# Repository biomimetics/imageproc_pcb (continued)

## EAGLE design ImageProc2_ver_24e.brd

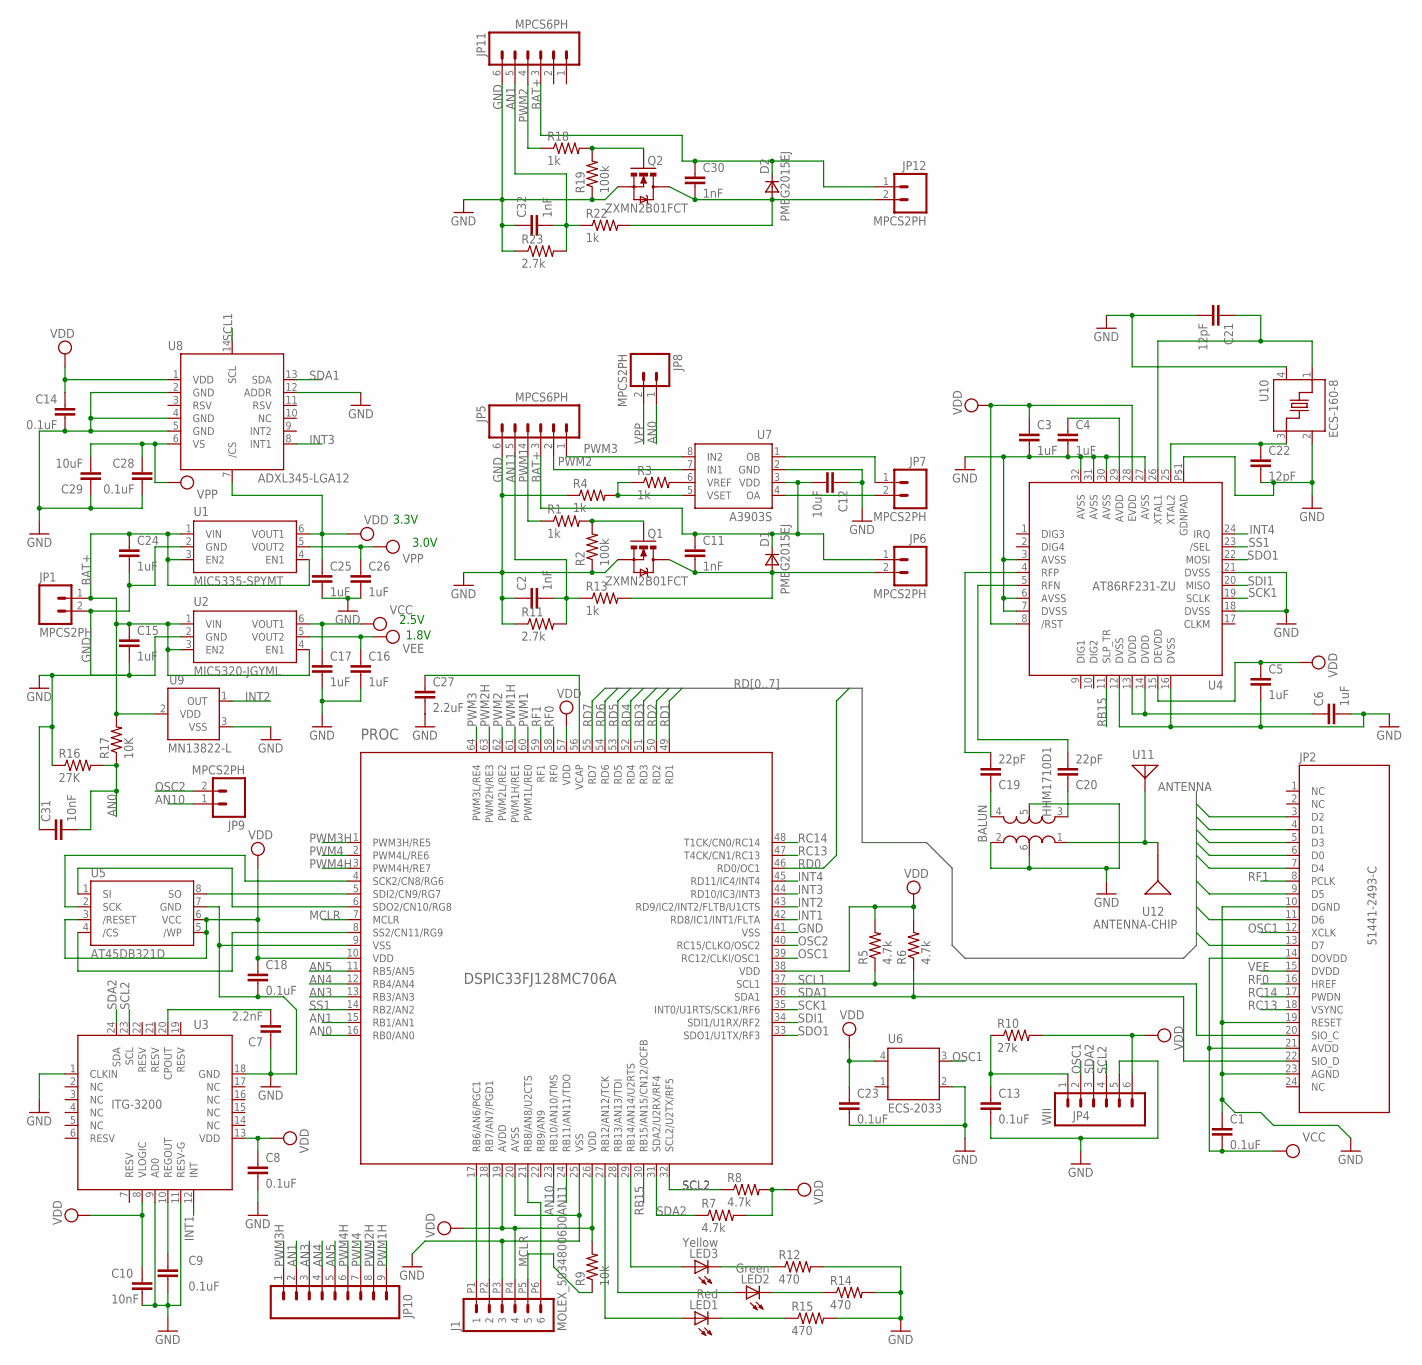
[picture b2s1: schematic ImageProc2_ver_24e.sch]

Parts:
BALUN: HHM1710D1; BALUN; DIGIKEY 445-3246-1-ND
C1, C8, C9, C13, C14, C18, C23, C28: 0.1uF; 0402-CAP; DIGIKEY 490-1318-1-ND
C2, C11, C30, C32: 1nF; 0402-CAP; DIGIKEY 490-1303-1-ND
C3, C4, C5, C6, C15, C16, C17, C24, C25, C26: 1uF; 0402-CAP; DIGIKEY 445-4998-1-ND
C7: 2.2nF; 0402-CAP; DIGIKEY 399-1033-1-ND
C10, C31: 10nF; 0402-CAP; DIGIKEY 399-1279-1-ND
C12, C29: 10uF; 0603-CAP; DIGIKEY 399-5504-1-ND
C19, C20: 22pF; 0402-CAP; DIGIKEY 490-1283-1-ND
C21, C22: 12pF; 0402-CAP; DIGIKEY 490-3115-1-ND
C27: 2.2uF; 0402-CAP; DIGIKEY C1005X5R0G225M
D1, D2: PMEG2015EJ; SOD323; DIGIKEY 568-4117-1-ND
J1: MOLEX_5034800600; DIGIKEY WM1387CT-ND
JP1, JP6, JP7, JP8, JP9, JP12: MPCS2PH; MOLEX-PICO_CLASP_S2P
JP2: 51441-2493-C; MOLEX-52740-2490; DIGIKEY WM1561-ND
JP4: WII; MOLEX-PICO_CLASP_S6P
JP5, JP11: MPCS6PH; MOLEX-PICO_CLASP_S6P
JP10: SOLDER_PADS_9P
LED1: Red; CHIP-LED0603; DIGIKEY 67-1690-1-ND
LED2: Green; CHIP-LED0603; DIGIKEY 67-1693-1-ND
LED3: Yellow; CHIP-LED0603; DIGIKEY 67-1694-1-ND
PROC: DSPIC33FJ128MC706A; TQFP64; DIGIKEY DSPIC33FJ128MC706A-I/PT-ND
Q1, Q2: ZXMN2B01FCT; SOT23-3; DIGIKEY ZXMN2B01FCT-ND
R1, R3, R4, R13, R18, R22: 1k; R0402; DIGIKEY P1.0KJCT-ND
R2, R19: 100k; R0402; DIGIKEY P100KJCT-ND
R5, R6, R7, R8: 4.7k; R0402; DIGIKEY P4.7KJCT-ND
R9: 10k; R0402; DIGIKEY P10KJCT-ND
R10: 27k; R0402; DIGIKEY P27KJCT-ND
R11, R23: 2.7k; R0402; DIGIKEY P2.7KJCT-ND
R12, R14, R15: 470; R0402; DIGIKEY 541-470JCT-ND
R16: 27K; R0402; DIGIKEY P27KJCT-ND
R17: 10K; R0402; DIGIKEY P10KJCT-ND
U1: MIC5335-SPYMT; MLF-6; DIGIKEY 576-1949-1-ND
U2: MIC5320-JGYML; MLF-6; DIGIKEY 576-3589-6-ND
U3: ITG-3200; QFN-24
U4: AT86RF231-ZU; QFN-32; DIGIKEY AT86RF231-ZU-ND
U5: AT45DB321D; MLF(VDFN)-8; DIGIKEY AT45DB321D-SU-ND
U6: ECS-2033; OSCILLATOR-SMD; DIGIKEY XC1437CT-ND
U7: A3903S; DFN-8; DIGIKEY 620-1205-1-ND
U8: ADXL345-LGA12; LGA14; DIGIKEY ADXL345BCCZ-RLCT-ND
U9: MN13822-L; SOT-23-3; DIGIKEY 497-6182-1-ND
U10: ECS-160-8; CRYSTAL-SMD; DIGIKEY ECS-160-20-33-CKM-TR
U11: ANTENNA; ANTENNA_PAD
U12: ANTENNA-CHIP; DIGIKEY 445-3719-1-ND

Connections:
AN0: C31.2, JP8.1, PROC.16 (RB0/AN0), R16.2, R17.1
AN1: C32.2, JP10.2, JP11.5, PROC.15 (RB1/AN1), R22.1, R23.2
AN3: JP10.3, PROC.13 (RB3/AN3)
AN4: JP10.4, PROC.12 (RB4/AN4)
AN5: JP10.5, PROC.11 (RB5/AN5)
AN10: JP9.1, PROC.23 (RB10/AN10/TMS)
AN11: C2.2, JP5.5, PROC.24 (RB11/AN11/TDO), R11.2, R13.1
BAT+: C11.1, C12.2, C15.1, C24.1, C30.1, D1.1 (C), D2.1 (C), JP1.1, JP5.3, JP6.1, JP11.3, JP12.1, R17.2, U1.1 (VIN), U1.3 (EN2), U1.4 (EN1), U2.1 (VIN), U2.3 (EN2), U2.4 (EN1), U7.3 (VDD), U9.2 (VDD)
GND: BALUN.2 (RFGND), BALUN.5 (GND), BALUN.6 (NC), C1.1, C2.1, C3.2, C4.2, C5.2, C6.2, C7.1, C8.2, C9.2, C10.2, C12.1, C13.2, C14.2, C15.2, C16.2, C17.2, C18.2, C21.2, C22.2, C23.2, C24.2, C25.2, C26.2, C27.2, C28.2, C29.1, C31.1, C32.1, J1.P3 (3), JP1.2, JP2.10 (DGND), JP2.19 (RESET), JP2.23 (AGND), JP4.5, JP5.6, JP11.6, PROC.9 (VSS), PROC.20 (AVSS), PROC.25 (VSS), PROC.41 (VSS), Q1.2 (S), Q2.2 (S), R2.1, R4.1, R11.1, R12.2, R14.2, R15.2, R16.1, R19.1, R23.1, U1.2 (GND), U2.2 (GND), U3.1 (CLKIN), U3.9 (AD0), U3.11 (RESV-G), U3.18 (GND), U4.3 (AVSS), U4.6 (AVSS), U4.7 (DVSS), U4.12 (DVSS), U4.16 (DVSS), U4.18 (DVSS), U4.21 (DVSS), U4.27 (AVSS), U4.30 (AVSS), U4.31 (AVSS), U4.32 (AVSS), U4.P$1 (GDNPAD), U5.7 (GND), U6.2 (GND), U7.2 (GND), U8.2 (GND), U8.4 (GND), U8.5 (GND), U8.12 (ADDR), U9.3 (VSS), U10.2 (GND), U10.4 (GND)
INT1: PROC.42 (RD8/IC1/INT1/FLTA), U3.12 (INT)
INT2: PROC.43 (RD9/IC2/INT2/FLTB/U1CTS), U9.1 (OUT)
INT3: PROC.44 (RD10/IC3/INT3), U8.8 (INT1)
INT4: PROC.45 (RD11/IC4/INT4), U4.24 (IRQ)
MCLR: J1.P5 (5), PROC.7 (MCLR), R9.1
unnamed: C27.1, PROC.56 (VCAP)
unnamed: PROC.6 (SDO2/CN10/RG8), U5.1 (SI)
unnamed: LED3.C, R12.1
unnamed: Q2.1 (G), R18.2, R19.2
unnamed: LED3.A, PROC.29 (RB14/AN14/U2RTS)
unnamed: LED2.C, R14.1
unnamed: LED1.C, R15.1
unnamed: LED2.A, PROC.28 (RB13/AN13/TDI)
unnamed: LED1.A, PROC.27 (RB12/AN12/TCK)
unnamed: Q1.1 (G), R1.2, R2.2
unnamed: C30.2, D2.2 (A), JP12.2, Q2.3 (D), R22.2
unnamed: C11.2, D1.2 (A), JP6.2, Q1.3 (D), R13.2
unnamed: JP7.1, U7.1 (OB)
unnamed: JP7.2, U7.4 (OA)
unnamed: J1.P1 (1), PROC.17 (RB6/AN6/PGC1)
unnamed: C4.1, U4.29 (AVDD)
unnamed: J1.P2 (2), PROC.18 (RB7/AN7/PGD1)
unnamed: R3.2, U7.6 (VREF)
unnamed: R3.1, R4.2, U7.5 (VSET)
unnamed: C6.1, U4.13 (DVDD), U4.14 (DVDD)
unnamed: C7.2, U3.20 (CPOUT)
unnamed: C9.1, U3.10 (REGOUT)
unnamed: PROC.4 (SCK2/CN8/RG6), U5.2 (SCK)
unnamed: BALUN.4 (BAL4), C19.1
unnamed: PROC.5 (SDI2/CN9/RG7), U5.8 (SO)
unnamed: BALUN.3 (BAL3), C20.1
unnamed: C19.2, U4.4 (RFP)
unnamed: PROC.8 (SS2/CN11/RG9), U5.4 (/CS)
unnamed: C20.2, U4.5 (RFN)
unnamed: C22.1, U4.25 (XTAL2), U10.3 (IN/OUT)
unnamed: C21.1, U4.26 (XTAL1), U10.1 (IN/OUT)
unnamed: BALUN.1 (UNBAL), U11.P$1, U12.SIG
unnamed: C13.1, JP4.1, R10.1
unnamed: J1.P6 (6), PROC.21 (RB8/AN8/U2CTS)
OSC1: JP2.12 (XCLK), JP4.2, PROC.39 (RC12/CLKI/OSC1), U6.3 (OUT)
OSC2: JP9.2, PROC.40 (RC15/CLKO/OSC2)
PWM1: JP5.4, PROC.60 (PWM1L/RE0), R1.1
PWM1H: JP10.9, PROC.61 (PWM1H/RE1)
PWM2: JP5.2, JP11.4, PROC.62 (PWM2L/RE2), R18.1, U7.7 (IN1)
PWM2H: JP10.8, PROC.63 (PWM2H/RE3)
PWM3: JP5.1, PROC.64 (PWM3L/RE4), U7.8 (IN2)
PWM3H: JP10.1, PROC.1 (PWM3H/RE5)
PWM4: JP10.7, PROC.2 (PWM4L/RE6)
PWM4H: JP10.6, PROC.3 (PWM4H/RE7)
RB15: PROC.30 (RB15/AN15/CN12/OCFB), U4.11 (SLP_TR)
RC13: JP2.18 (VSYNC), PROC.47 (T4CK/CN1/RC13)
RC14: JP2.17 (PWDN), PROC.48 (T1CK/CN0/RC14)
RD0: JP2.6 (D0), PROC.46 (RD0/OC1)
RD1: JP2.4 (D1), PROC.49 (RD1)
RD2: JP2.3 (D2), PROC.50 (RD2)
RD3: JP2.5 (D3), PROC.51 (RD3)
RD4: JP2.7 (D4), PROC.52 (RD4)
RD5: JP2.9 (D5), PROC.53 (RD5)
RD6: JP2.11 (D6), PROC.54 (RD6)
RD7: JP2.13 (D7), PROC.55 (RD7)
RF0: JP2.16 (HREF), PROC.58 (RF0)
RF1: JP2.8 (PCLK), PROC.59 (RF1)
SCK1: PROC.35 (INT0/U1RTS/SCK1/RF6), U4.19 (SCLK)
SCL1: JP2.20 (SIO_C), PROC.37 (SCL1), R5.1, U8.14 (SCL)
SCL2: JP4.4, PROC.32 (SCL2/U2TX/RF5), R8.1, U3.23 (SCL)
SDA1: JP2.22 (SIO_D), PROC.36 (SDA1), R6.1, U8.13 (SDA)
SDA2: JP4.3, PROC.31 (SDA2/U2RX/RF4), R7.1, U3.24 (SDA)
SDI1: PROC.34 (SDI1/U1RX/RF2), U4.20 (MISO)
SDO1: PROC.33 (SDO1/U1TX/RF3), U4.22 (MOSI)
SS1: PROC.14 (RB2/AN2), U4.23 (/SEL)
VCC: C1.2, C17.1, JP2.14 (DOVDD), JP2.21 (AVDD), U2.6 (VOUT1)
VDD: C3.1, C5.1, C8.1, C10.1, C14.1, C18.1, C23.1, C25.1, J1.P4 (4), JP4.6, PROC.10 (VDD), PROC.19 (AVDD), PROC.26 (VDD), PROC.38 (VDD), PROC.57 (VDD), R5.2, R6.2, R7.2, R8.2, R9.2, R10.2, U1.6 (VOUT1), U3.8 (VLOGIC), U3.13 (VDD), U4.8 (/RST), U4.15 (DEVDD), U4.28 (EVDD), U5.3 (/RESET), U5.5 (/WP), U5.6 (VCC), U6.4 (VDD), U8.1 (VDD), U8.7 (/CS)
VEE: C16.1, JP2.15 (DVDD), U2.5 (VOUT2)
VPP: C26.1, C28.1, C29.2, JP8.2, U1.5 (VOUT2), U8.6 (VS)

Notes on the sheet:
3.3V
2.5V
1.8V
3.0V

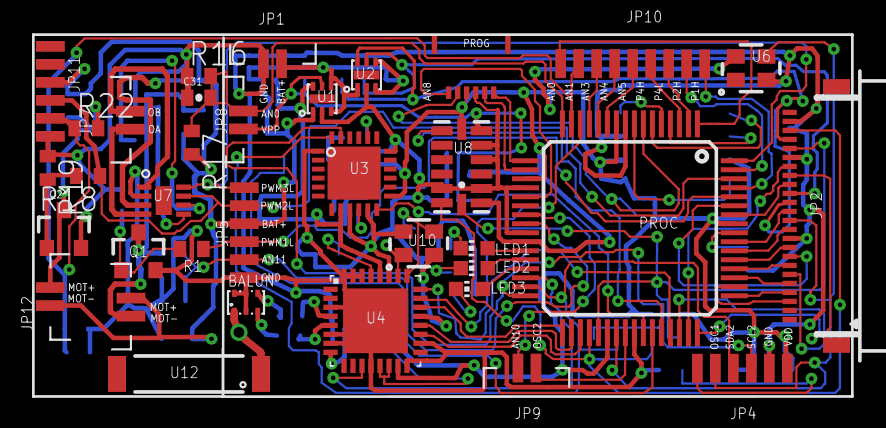
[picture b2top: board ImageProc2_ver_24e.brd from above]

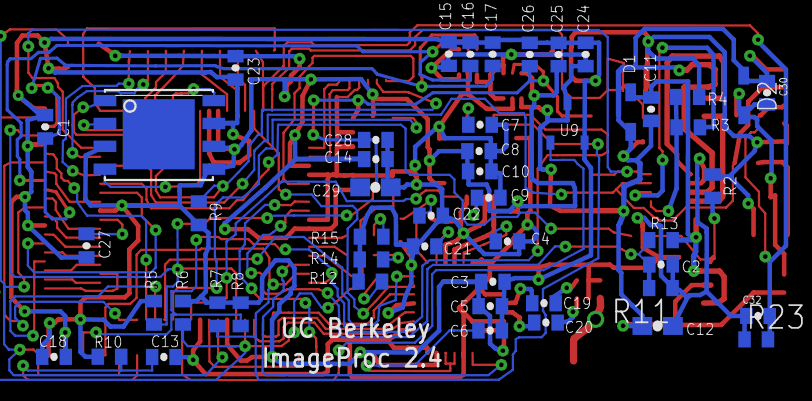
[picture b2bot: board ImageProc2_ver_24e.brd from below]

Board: 2 copper layers, 86 parts (50 on the bottom side), 83 nets.

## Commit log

2012-05-09 Redacting readme.
2012-05-09 Minor readme updates.
2012-05-09 Yet another minor readme update.
2012-05-09 Updated readme.
2012-05-09 Added camera breakout board.
2012-05-09 Added ImageProc1 and MotorDriver1 pcbs, superseding the CameraBreakout board.
2012-05-09 Added ImageProc2, superseding ImageProc1+MotorDriver1.
2012-05-09 Added ImageProc2.24.
2012-05-09 Added Eagle libraries.
2012-05-09 Minor readme update.
2012-05-10 Getting rid of ImageProc folder, for now.
2012-05-22 Minor update of README.rst
2012-06-16 *Added biomimetic.lbr (only has schematic frame for now) *Added initial schematics and old layout *Added 66each design rules *Began separating schematic elements info different sheets
2012-06-29 Stopped commiting for a week. Oops.
2012-06-29 Stopped committing for a week. Oops.
2012-06-30 Before work 6/30
2012-06-30 Work 6/30
2012-06-30 Commit before replace LTC6088 with LT1991
2012-07-02 Partial motor driver route. Motor drive vias moved to edge (could be used for strain relief).
2012-07-02 Motor section mostly complete, except motor controller power and PIC analog pins. Camera connector escape complete. Edited PIC keepout to be tighter.
2012-07-03 Partial antenna and RF route. Adjusted ground planes to avoid antenna and moved antenna to lower-right corner, moved OVCAM connector up to make room.
2012-07-03 RF top layout complete
2012-07-03 Added tPlace outlines to 0603s and 0402s
2012-07-04 Partial IMU/flash route. PIC, IMU, and flash locations locked. Passives for IMU/flash.
2012-07-05 Motor section mostly complete. Board expanded. PIC passives mostly complete.
2012-07-07 PIC and radio vias added. Partial camera route.
2012-07-07 More camera connector routed. Vias on right side of PIC re-spaced.
2012-07-09 Added anti-aliasing filter values (not sure how I missed those). Renamed external pins.
2012-07-09 Remove cam, lbr, dru directories.
2012-07-09 Added DRUs, CAMs, and LBRs back in (decided to merge repositories).
2012-07-09 Added DRUs, CAMs, and LBRs back in (decided to merge repositories). (reverse-merged from commit 1759a90b045de7ea167f3af36a0b0839201c0690)
2012-07-10 first few routes on ground
2012-07-10 first few traces on ground
2012-07-13 Routed Several more connections.
    Placed LEDS and added vias for it.
    Placed Connector On Bottom.
    Deleted some badly planned connections from last time.
2012-07-13 More routs seperated jp3 and the 2 7-pin components
2012-07-13 Moved an LED
    Added wires to ground plane
2012-07-13 Removed incorrectly wired bypass caps on the regulators
2012-07-13 placed and wired the bypass caps for the 2 regulators.
    Placed and wired the voltage divider on sheet 1 of the schematic
2012-07-15 34 air wires left.
    Espescially improved area around mpu 6000
    Running into problems with areas of the 3.3 and GND planes being cutoff due to many traces in their planes.
    Next step: shift wires in the ground plane near the mpu6000 to allow for vias in the groundplane to carry the pad outputs.
2012-07-15 commmit of the last commit????
2012-07-16 ran DRC, fixed DRC issues for top and ground.
2012-07-16 Fixed rest of the initial DRC errors.
    Down to 24 air wires.
    Having to be creative for the pads.
2012-07-17 17 airwires left.
    did most of the wiring of the pads && the relocating of various ground and power layer wires to compensate.
2012-07-17 3 airwires left….
    begun fixing the airwires in the motor controller section
2012-07-17 Zero Airwires, fixed the restrict DRC errors.
    Now proceeding to (hopefully final) DRC
2012-07-18 0 Airwires, 0 non-ignored DRC Errors.
2012-07-18 Adding dual FET driver variant of ImageProc2 board.
2012-07-18 Adding dual FET driver + new FPC ZIF programming connector variant of ImageProc2 board.
2012-08-15 ImageProc 2.5 Rev. A
    Final silk screen and manufacturing modifications. Submitted for
    prototype manufacturing on 7/26/2012.
    ImageProc 2.5 updates the ImageProc with several new features and updated
    silicon, while focusing on on enhanced manufacturability and ease of
    modification. Software revisions to the octoroach and imageproc-lib codebases
    are forthcoming.
2012-08-15 Rename ImageProc_2.5.* to ImageProc.*
2012-08-15 Added sheet name headings
2012-08-15 Re-added clobbered README.rst
2012-08-15 Fix README formatting
2012-08-15 Fix typo added after clobbering readme
2012-08-23 Initial commit of the erratta.
    hardware verified: Power, dpsic, radio, both h-bridges, LED.
2012-08-27 Resolved the three wiring issues (non-connect on the v_batt plane, non-connect for a logic ground, and programming connector backwards).
    Added the biomimetics dru's
2012-08-27 Nudged the outside vias and pads to get sufficient edge clearance.
2012-08-27 Changed the revision letter in the silkscreen to "B".
2012-09-03 Added a 4th (albiet minor) erratta concerning C37 and C40.
2012-09-03 Fixed many of 2.5 A's erratta, to form 2.5B.
    Fixed the top motor controller's missing GND pin.
    Fixed the Radio Chip's pins that were combined.
    Fixed C37/C40 mislabeling.
2012-09-03 Updated this schematic to revision 2.5B.
    Changed the revision # in the bottom right corner.
    Also modified to fix the motor controller Ground pin issue.
2012-09-14 Added Pads for PWM 1 and 2 to MOTOR_C_IN_2 and MOTOR_D_IN_2 on the top.
    Added this both to the schematic and routed it on the board.
2012-09-17 Remove dru folder, update .gitignore
2012-09-18 Update PCB date, correct bridge on AT86RF233
2012-09-29 Added Digi-Key part numbers to ImageProc2.4e
2012-10-23 Fix transposed SDA1/SCL1 on dsPIC
2012-12-14 Pinouts spread sheet updated for IP 2.5c
2012-12-15 changed comment in .xls to current date
2013-02-01 Create Pinout.md
    Table of dsPIC pin/port assignments, as well at net names and plain
    english descriptions.
2013-02-01 Update Pinout.md
    Added port usage
2013-02-01 Update Pinout.md
    Add net names.
2013-02-01 Update Pinout.md
    Edit plain english descriptions
2013-02-01 Remove pinout Excel spreadsheet
    Superceded by Pinout.md
2013-02-01 Correct typo in Pinout.md
2013-02-01 Update datecode for new order
2013-05-31 Add BOM and CPL
2014-04-23 Changed layer state for schematic.
2014-04-23 Added documentation pack PDF.
